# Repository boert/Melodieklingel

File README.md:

# Melodieklingel

Leiterplatte für die Melodieklingel nach der Veröffentlichung von S. Lehmann im Funkamateur 4/86

## Eckdaten
Leiterplattengröße: 100 x 100 mm  
Betriebsspannung: 5V DC  
Stromaufnahme: 87 bis 230 mA (min./max.)  
Schaltschwelle (Transistor):   1,4 V  
Schaltschwelle (Optokoppler):  8 V (DC) oder 5,6 V (AC)    

### Anschlüsse

| Name      | Bedeutung                 | Bemerkung                                         |
| -----     | ---------                 | ---------                                         |
| TP 0      | GND/ Masse                |                                                   |
| TP 1      | Eingang Transistorstufe   | nicht potentialfrei, max. 24V Eingangsspannung    |
| TP 2      | Ausgang Transistorstufe   | muß ggf. mit TP3 verbunden werden                 |
| TP 3      | Taster                    | nicht potentialfrei, max. 5V Eingangsspannung     |
| TP 4      | Lautsprecher              |                                                   |
| TP 5      | +5V                       |                                                   |
| TP 100    | Eingang Optokoppler (+)   | potentialfrei, max. 24V Eingangsspannung          |
| TP 101    | Eingang Optokoppler (-)   | potentialfrei, max. 24V Eingangsspannung          |
| TP 102    | Ausgang Optokoppler       | muß ggf. mit TP3 verbunden werden                 |

Der zweite Anschluss des Lautsprechers muß mit +5V (TP5) verbunden werden.

### Stromaufnahme

Alle Messungen erfolgten mit einem 8 Ohm-Kleinlautsprecher.

| Logikfamilie | IC D1   | IC D2     | IC D3 | IC D4   | Ruhezustand      | Wiedergabe       |
| ------------ | ------- | --------- | ----- | ------  | ----------------:| ----------------:|
| TTL          | D104    | U880D     | U2716 | D174    | 183 mA  (0,92 W) | 230 mA  (1,15 W) |
| CMOS         | 74HCT04 | STZ8400   | U2716 | 74LS74  | 128 mA  (0,64 W) | 175 mA  (0,88 W) |
| CMOS         | 74HCT04 | TMPZ84C00 | U2716 | 74LS74  |  87 mA  (0,44 W) | 135 mA  (0,68 W) | 

Hinweis: Da bei D4 nicht alle Eingänge beschaltet wurden, kann es beim Einsatz von 74HCT74 zu Fehlfunktionen kommen. Bei Verwendung von DL074/74LS74 sollte es keine Probleme geben.

## Änderungen gegenüber dem Original
- zusätzliche Bestückungsvariante mit Optokoppler zur galvanischen Trennung des Klingel
- Werte und Baugrößen an vorhandenen Lagerbestand angepasst
- alle liegenden Widerstände auf 15 mm Rastermaß geändert
- Stützkondensator für U880D ergänzt

## Bestückungsvarianten
### Taster
Dieser wird zwischen den Lötpunkten 'Start' und 'GND' angeschlossen.
Da keine galvansiche Trennung und Entstörung vorliegt, eignet sich diese Variante nur für denn Fall, das der Taster mit einer kurzen Leitung angschlossen wird, z.B. bei einer Montage im Gehäuse.

Folgende Bauteile können bei der Bestückung entfallen:  
C3, C4, R5, R6, VD1, VT1  
sowie:  
R100, R101, D100, VD100  

### Transistor
Bei dieser Variante hilft ein Tiefpass und ein Transistor beim Auslösen der Klingel. Es muß eine Verbindung zwischen TP2 und TP3 hergetellt werden.
Als Transistor für VT1 eignet sich jeder beliebige Kleinsignal-NPN-Typ, z.B. SC236, SF126, SF136, SF357, SS125, SS216.

Folgende Bauteile können bei der Bestückung entfallen:  
R100, R101, D100, VD100  

### Optokoppler
Hier wird ein Optokoppler zur galvaischen Trennung genutzt.
Um diese Variante zu Nutzen muß eine Verbindung zwischen TP102 und TP3 hergetellt werden.  
Zum Auslösen der Klingel dient die Gleich- oder Wechselspannung der vorhandenen Klingelanlage. Die Klingel wird mit einem Signal ab 8 V Gleichspannung oder ab 5,6 V Wechselspannung aktiviert. Über den Widerstand R100 kann die Schaltschwelle angepasst werden.  

Der Widerstand R7 sollte ggf. auf 47 kOhm erhöht werden, damit der Pegel am Gatter D1B passt.  
Folgende Bauteile können bei der Bestückung entfallen:  
C3, C4, R5, R6, VD1, VT1  

## Links
https://hc-ddr.hucki.net/wiki/doku.php/elektronik/melodieklingel

# Änderungen / History
## Version 3, 28.12.2022
- VT2, Footprint korrigiert (180° gedreht)

## Version 2, 29.11.2022
- C1 von 470 nF zu 470 pF geändert   
- D100, Pin 5 und Pin 6 getauscht

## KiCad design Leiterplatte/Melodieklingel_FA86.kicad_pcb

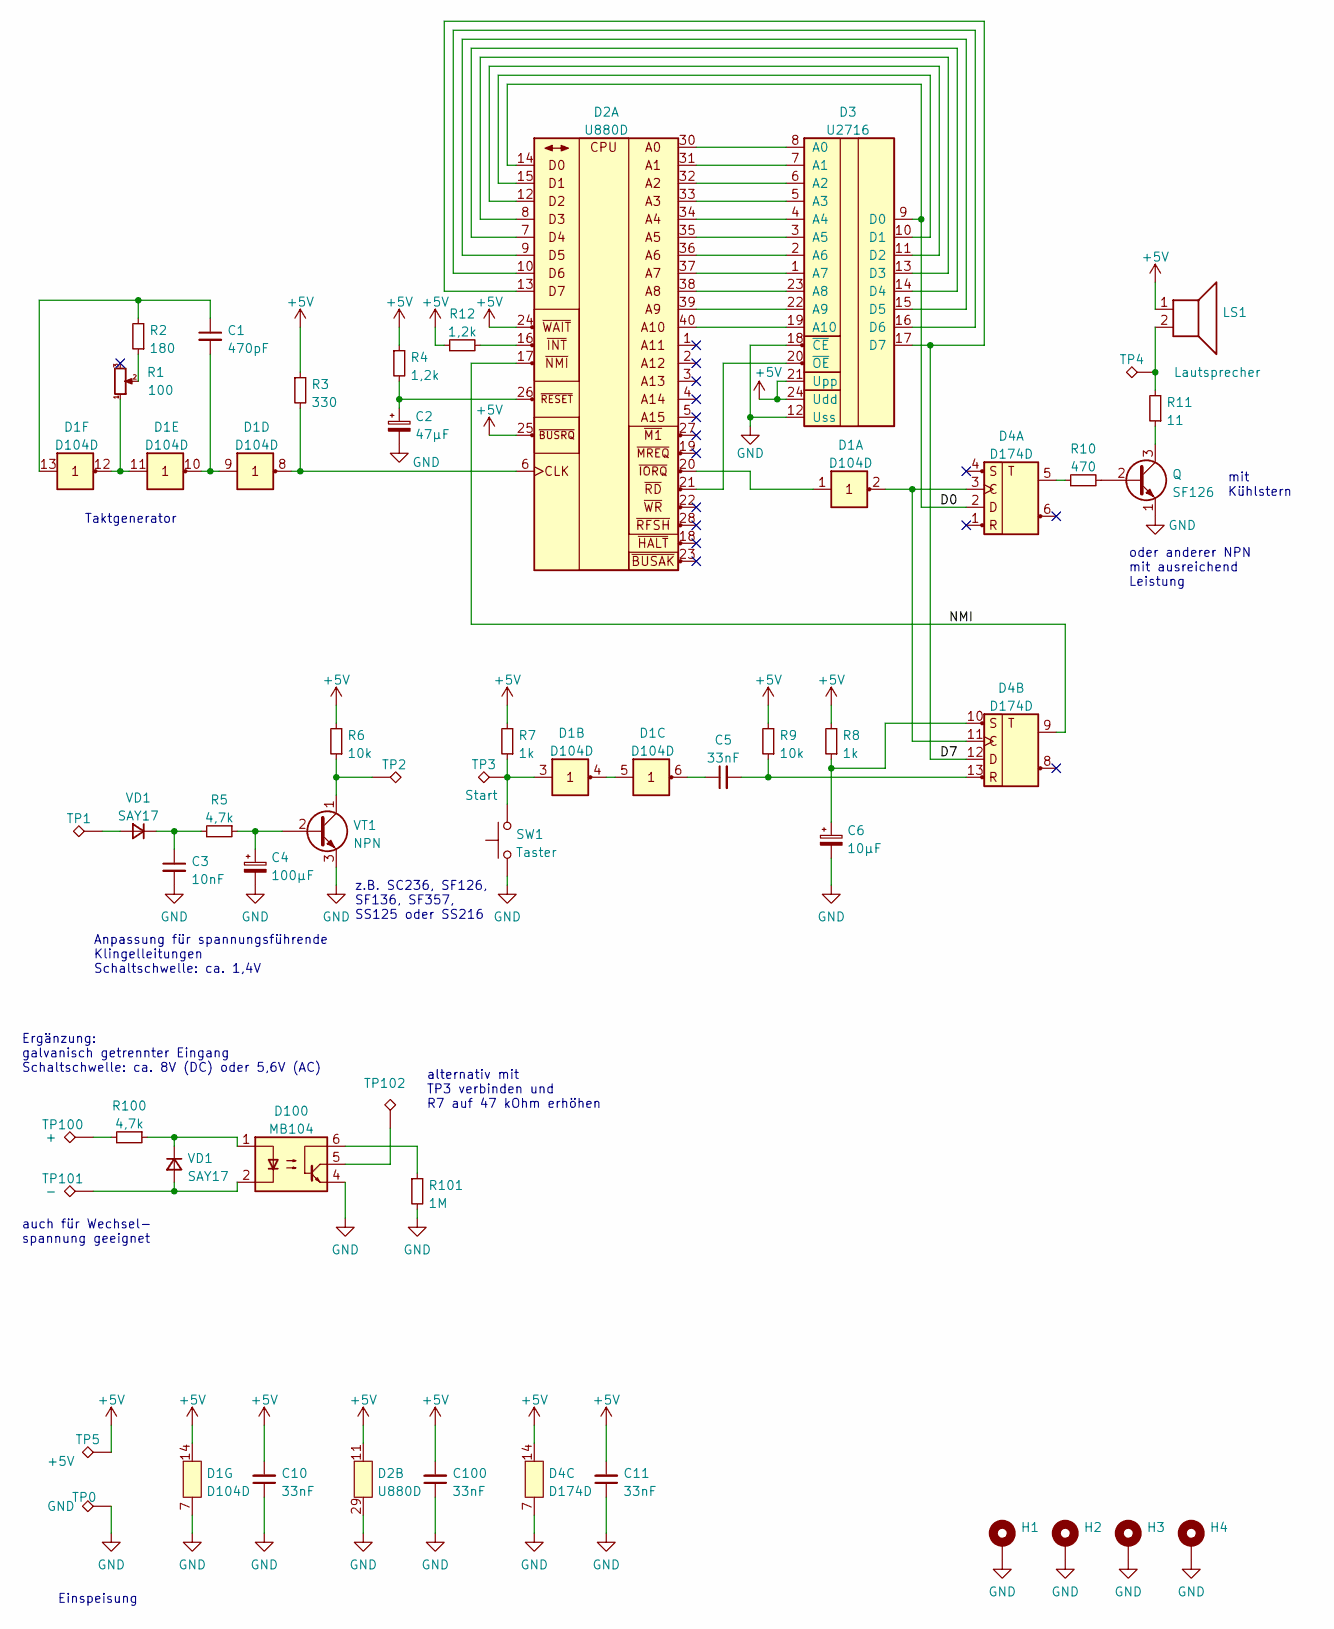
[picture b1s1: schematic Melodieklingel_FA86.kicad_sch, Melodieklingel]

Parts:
C1: 470nF; C_Rect_L18.0mm_W7.0mm_P15.00mm_FKS3_FKP3
C2: 47µF; CP_Radial_D5.0mm_P2.50mm
C3: 10nF; C_Disc_D5.0mm_W2.5mm_P2.50mm
C4: 100µF; CP_Radial_D8.0mm_P3.50mm
C5, C10, C11, C100: 33nF; C_Disc_D8.0mm_W2.5mm_P5.00mm
C6: 10µF; CP_Axial_L21.0mm_D8.0mm_P28.00mm_Horizontal
D1: D104D; DIP-14_W7.62mm_LongPads
D2: U880D; DIP-40_W15.24mm_LongPads
D3: U2716; DIP-24_W15.24mm_LongPads
D4: D174D; DIP-14_W7.62mm_LongPads
D100: MB104; DIP-6_W7.62mm_LongPads
H1, H2, H3, H4: MountingHole_Pad; MountingHole_3.7mm_Pad_Via
LS1: Lautsprecher
Q: SF126; TO-5-3
R1: 100; Potentiometer_Bourns_3296W_Vertical
R2: 180; R_Axial_DIN0207_L6.3mm_D2.5mm_P5.08mm_Vertical
R3: 330; R_Axial_DIN0207_L6.3mm_D2.5mm_P15.24mm_Horizontal
R4: 1,2k; R_Axial_DIN0411_L9.9mm_D3.6mm_P5.08mm_Vertical
R5, R100: 4,7k; R_Axial_DIN0207_L6.3mm_D2.5mm_P15.24mm_Horizontal
R6, R9: 10k; R_Axial_DIN0207_L6.3mm_D2.5mm_P15.24mm_Horizontal
R7, R8: 1k; R_Axial_DIN0411_L9.9mm_D3.6mm_P15.24mm_Horizontal
R10: 470; R_Axial_DIN0411_L9.9mm_D3.6mm_P15.24mm_Horizontal
R11: 11; R_Axial_DIN0207_L6.3mm_D2.5mm_P15.24mm_Horizontal
R12: 1,2k; R_Axial_DIN0411_L9.9mm_D3.6mm_P15.24mm_Horizontal
R101: 1M; R_Axial_DIN0207_L6.3mm_D2.5mm_P5.08mm_Vertical
SW1: Taster
TP0: GND; TestPoint_THTPad_2.5x2.5mm_Drill1.2mm
TP1: Eingang; TestPoint_THTPad_2.5x2.5mm_Drill1.2mm
TP2, TP102: Ausgang; TestPoint_THTPad_2.5x2.5mm_Drill1.2mm
TP3: Start; TestPoint_THTPad_2.5x2.5mm_Drill1.2mm
TP4: Lautsprecher; TestPoint_THTPad_2.5x2.5mm_Drill1.2mm
TP5: +5V; TestPoint_THTPad_2.5x2.5mm_Drill1.2mm
TP100: +; TestPoint_THTPad_2.5x2.5mm_Drill1.2mm
TP101: -; TestPoint_THTPad_2.5x2.5mm_Drill1.2mm
VD1: SAY17; D_E-Line_P2.5mm_Vertical
VT1: NPN; T_E-Line_Wide_P2.5mm_Vertical

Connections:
+5V: C10.2, C11.2, C100.2, D1.14 (Vcc), D2.11 (Vcc), D2.24 (~WAIT), D2.25 (~BUSRQ), D3.21 (Upp), D3.24 (Udd), D4.14 (Vcc), LS1.1, R3.1, R4.1, R6.2, R7.2, R8.2, R9.2, R12.1, TP5.1
/D0: D2.14 (D0), D3.9 (D0), D4.2 (D1)
/D7: D2.13 (D7), D3.17 (D7), D4.12 (D2)
/NMI: D2.17 (~NMI), D4.9 (Q2)
GND: C2.2, C3.2, C4.2, C6.2, C10.1, C11.1, C100.1, D1.7 (GND), D2.29 (GND), D3.12 (Uss), D3.18 (~CE), D4.7 (GND), D100.4, H1.1, H2.1, H3.1, H4.1, Q.1 (E), R101.2, SW1.1, TP0.1, VT1.3 (E)
unnamed: C1.1, D1.13 (A6), R2.2
unnamed: C1.2, D1.9 (A4), D1.10 (Y5)
unnamed: C2.1, D2.26 (~RESET), R4.2
unnamed: C4.1, R5.1, VT1.2 (B)
unnamed: C5.1, D1.6 (Y3)
unnamed: C5.2, D4.13 (R2), R9.1
unnamed: C6.1, D4.10 (S2), R8.1
unnamed: D1.1 (A1), D2.20 (~IORQ)
unnamed: D1.2 (Y1), D4.3 (T1), D4.11 (T2)
unnamed: D1.3 (A2), R7.1, SW1.2, TP3.1
unnamed: D1.4 (Y2), D1.5 (A3)
unnamed: D1.8 (Y4), D2.6 (CLK), R3.2
unnamed: D1.11 (A5), D1.12 (Y6), R1.1
unnamed: D2.7 (D4), D3.14 (D4)
unnamed: D2.8 (D3), D3.13 (D3)
unnamed: D2.9 (D5), D3.15 (D5)
unnamed: D2.10 (D6), D3.16 (D6)
unnamed: D2.12 (D2), D3.11 (D2)
unnamed: D2.15 (D1), D3.10 (D1)
unnamed: D2.16 (~INT), R12.2
unnamed: D2.21 (~RD), D3.20 (~OE)
unnamed: D2.30 (A0), D3.8 (A0)
unnamed: D2.31 (A1), D3.7 (A1)
unnamed: D2.32 (A2), D3.6 (A2)
unnamed: D2.33 (A3), D3.5 (A3)
unnamed: D2.34 (A4), D3.4 (A4)
unnamed: D2.35 (A5), D3.3 (A5)
unnamed: D2.36 (A6), D3.2 (A6)
unnamed: D2.37 (A7), D3.1 (A7)
unnamed: D2.38 (A8), D3.23 (A8)
unnamed: D2.39 (A9), D3.22 (A9)
unnamed: D2.40 (A10), D3.19 (A10)
unnamed: D4.5 (Q1), R10.1
unnamed: D100.5, TP102.1
unnamed: D100.6, R101.1
unnamed: LS1.2, R11.2, TP4.1
unnamed: R1.2, R2.1
unnamed: R6.1, TP2.1, VT1.1 (C)
unnamed: Q.2 (B), R10.2
unnamed: Q.3 (C), R11.1
unnamed: R100.2, TP100.1

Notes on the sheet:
auch für Wechsel- spannung geeignet
Ergänzung: galvanisch getrennter Eingang Schaltschwelle: ca. 8V (DC) oder 5,6V (AC)
mit Kühlstern
Einspeisung
oder anderer NPN mit ausreichend Leistung
alternativ mit TP3 verbinden und R7 auf 47 kOhm erhöhen
Anpassung für spannungsführende Klingelleitungen Schaltschwelle: ca. 1,4V
Taktgenerator
z.B. SC236, SF126, SF136, SF357, SS125 oder SS216

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
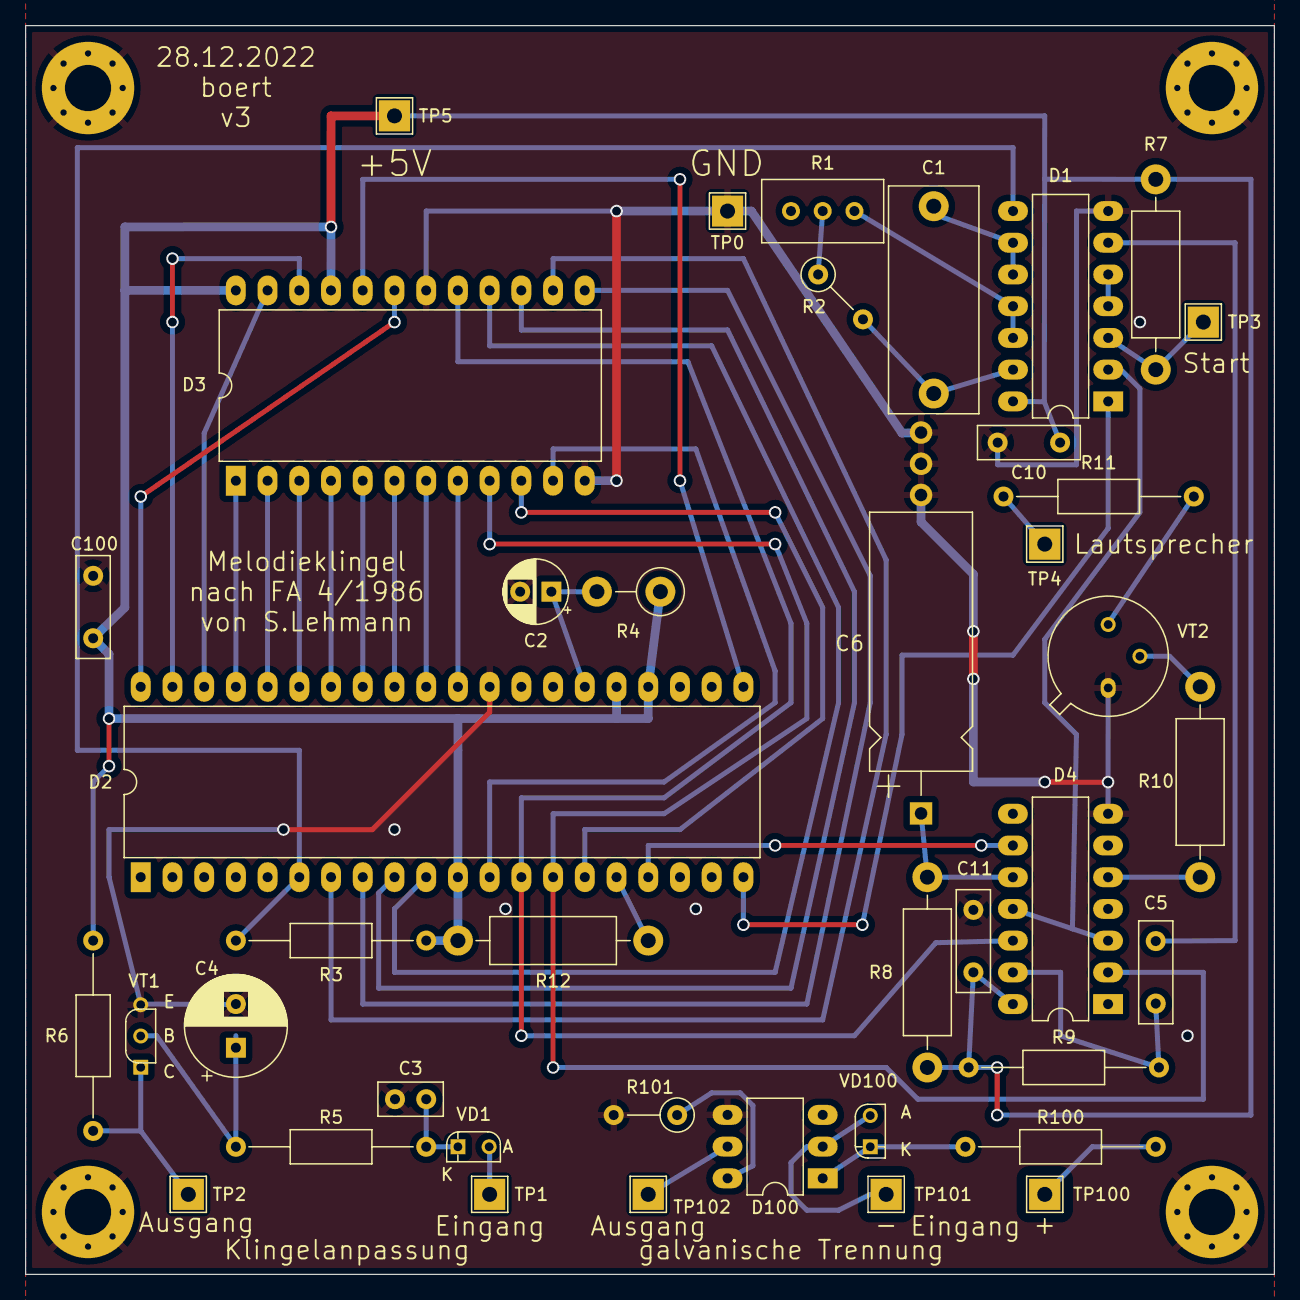
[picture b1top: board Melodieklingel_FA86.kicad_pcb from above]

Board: 2 copper layers, 100.0 x 100.0 mm, 45 parts (0 on the bottom side), 50 nets.

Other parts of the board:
VD1#2: SAY17; D_E-Line_P2.5mm_Vertical

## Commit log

2022-11-16 Leiterplattenprojekt ergänzt
2022-11-16 add: Vorschaubild
2022-11-16 update: Vorschau
2022-11-30 Leiterplatte v2, mit Korrekturen
2022-12-04 Verbrauchsmessungen ergänzt
2022-12-04 EPROM-Inhalte hinzugefügt
2022-12-04 Korrektur
2022-12-08 add: weitere Melodie-Eproms
2022-12-28 fix: VT2, Footprint
2023-04-05 add: Anschlußbelegung
